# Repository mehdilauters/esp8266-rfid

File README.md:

# ID-12LA to tcp bridge
http://cdn.sparkfun.com/datasheets/Sensors/ID/ID-2LA,%20ID-12LA,%20ID-20LA2013-4-10.pdf

Configure your parameters in user/user_config.h

run on your server 

````
python /tmp/server.py 5555
starting up on 0.0.0.0 port 5555
waiting for a connection
client connected:waiting for a connection
 ('54.145.90.17', 44844)
tag 7800F011A6 received
tag 7800F8CC97 received
````

To enable the webui, please run ````bower install first````

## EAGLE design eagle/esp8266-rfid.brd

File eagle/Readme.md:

https://www.sparkfun.com/tutorials/119

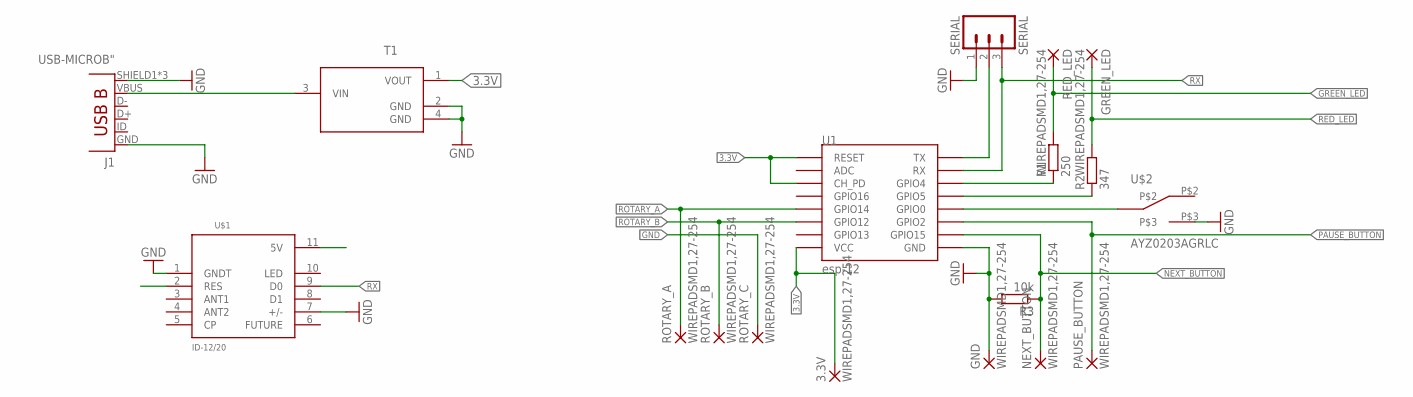
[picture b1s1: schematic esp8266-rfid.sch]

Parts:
3.3V: WIREPADSMD1,27-254; SMD1,27-2,54
GND: WIREPADSMD1,27-254; SMD1,27-2,54
GREEN_LED: WIREPADSMD1,27-254; SMD1,27-2,54
J1: USB-MICROB"; USB-B-MICRO-SMD_V03
NEXT_BUTTON: WIREPADSMD1,27-254; SMD1,27-2,54
PAUSE_BUTTON: WIREPADSMD1,27-254; SMD1,27-2,54
R1: 250; R0603
R2: 347; R0603
R3: 10k; R0603
RED_LED: WIREPADSMD1,27-254; SMD1,27-2,54
ROTARY_A: WIREPADSMD1,27-254; SMD1,27-2,54
ROTARY_B: WIREPADSMD1,27-254; SMD1,27-2,54
ROTARY_C: WIREPADSMD1,27-254; SMD1,27-2,54
SERIAL: SERIAL; 1X03
T1: L78L33ACUTR; SOT150P400X160-4N
U1: esp-12; ESP12-SMD
U$1: ID-12/20; ID-12
U$2: AYZ0203AGRLC

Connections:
3.3V: 3.3V.1, T1.1 (VOUT), U1.CH_PD, U1.RESET, U1.VCC
GND: GND.1, J1.GND, J1.SHIELD1 (SHIELD), J1.SHIELD2 (SHIELD), J1.SHIELD3 (SHIELD), R3.2, ROTARY_C.1, SERIAL.1, T1.2 (GND), T1.4 (GND), U1.GND, U$1.1 (GNDT), U$1.7 (+/-), U$2.P$3
GREEN_LED: R1.2, RED_LED.1
unnamed: U1.GPIO0, U$2.P$1 (COM)
unnamed: R1.1, U1.GPIO4
NEXT_BUTTON: NEXT_BUTTON.1, R3.1, U1.GPIO15
PAUSE_BUTTON: PAUSE_BUTTON.1, U1.GPIO2
RED_LED: GREEN_LED.1, R2.2
RESET: R2.1, U1.GPIO5
ROTARY_A: ROTARY_A.1, U1.GPIO14
ROTARY_B: ROTARY_B.1, U1.GPIO12
RX: SERIAL.3, U1.RXD0 (RX), U$1.9 (D0)
TX: SERIAL.2, U1.TXD0 (TX)
VBUS: J1.VBUS, T1.3 (VIN), U$1.2 (RES), U$1.11 (5V)

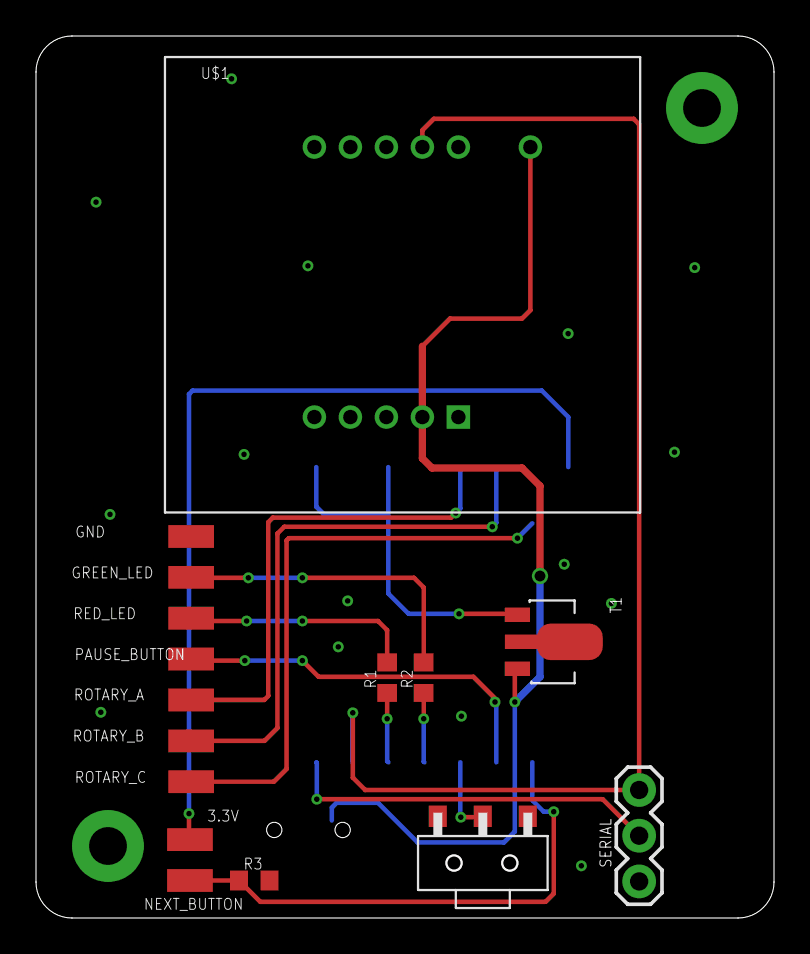
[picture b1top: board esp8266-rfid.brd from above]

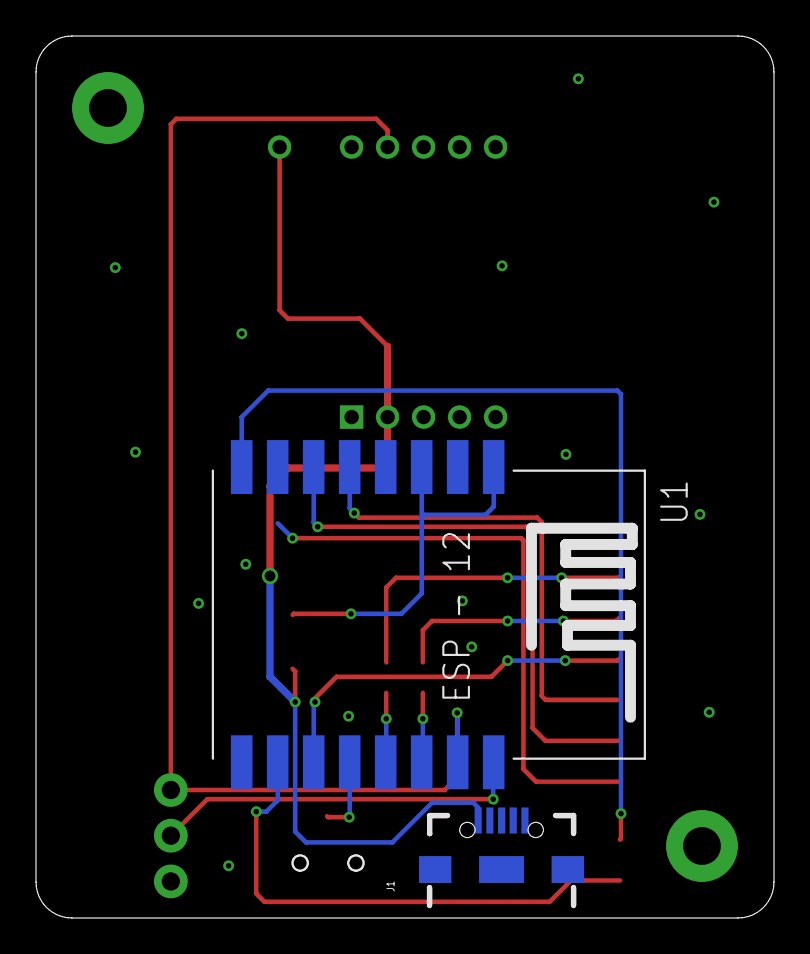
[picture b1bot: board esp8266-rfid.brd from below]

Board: 2 copper layers, 40.9 x 48.9 mm, 18 parts (2 on the bottom side), 14 nets.

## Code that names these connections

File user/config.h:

#ifndef CONFIG_HPP
#define CONFIG_HPP

#define DEFAULT_SSID "esp-rfid"

// should be firmwar_1.bin on the server
#define TFTP_IMAGE_FILENAME "esp-rfid.bin"

#define MAX_AP_DURATION 60

#define ALTERNATE_PUSH_PIN 0
#define PLAYPAUSE_PUSH_PIN 2
#define GREEN_LED_PIN 4
#define RED_LED_PIN 5

#define ROTARY_B 12
#define ROTARY_C 13
#define ROTARY_A 14

#define NEXT_PUSH_PIN 15



#define BUTTON_PRESSED_DELAY 100

#define UP_TAG "AF00AF00AC"
#define DOWN_TAG "AF00AF00AD"
#define NEXT_TAG "AF00AF00AE"
#define PAUSE_TAG "AF00AF00AF"

#define ALTERNATE_TAG "AF00AF00BA"
#define UP_ALTERNATE_TAG "AF00AF00BB"
#define DOWN_ALTERNATE_TAG "AF00AF00BC"
#define NEXT_ALTERNATE_TAG "AF00AF00BD"
#define PAUSE_ALTERNATE_TAG "AF00AF00BD"

#define RAW_TCP
#endif

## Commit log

2016-10-08 Serveur update
2016-10-08 RFIDServer
2016-10-08 New TCP connexion for each tag + virtal tag for button
2016-10-08 README
2016-10-08 missing file fix
2016-10-08 Default config file
2016-11-06 Adding EAGLE schematic
2016-11-11 EAGLE moved to new folder
2016-11-21 CONFIG: apmode if no config
2016-11-22 WEBUI: wifi settings begins to work
2016-11-23 WEBUI: parsing essid done
2016-11-23 WEBUI: working essid and passwprd setup
2016-11-24 WEBUI: saving server to flash
2016-11-25 WEBUI: security check + CONFIG: read server from flash
2016-11-28 WEBUI: adding current config
2016-11-28 WEBUI: captive portal configuration
2016-11-29 OTA: init
2016-12-01 SDK switch to rtos
2016-12-01 SDK switch WEBSERVER init
2016-12-05 WEBUI: parsing post request
2016-12-06 SDK: porting rfid.c
2016-12-07 ESP-12: update flash layout
2016-12-08 RFID: fix wifi hangs #1
2016-12-08 SDK: uart working
2016-12-15 OTA: first working solution
2016-12-19 APP: wifi task
2016-12-20 OTA: upgrade from client ip
2016-12-20 TEST prod
2016-12-21 TEST prod + upgrade check
2016-12-21 UPG from hmi: wip
2016-12-23 Serial number in HMI + baudrate
2016-12-23 OTA: upg fix
2016-12-27 EAGLE + http push
2016-12-27 EAGLE: rotary fix
2016-12-27 ROTARY init
2016-12-28 ROTARY_ENCODER + red led
2016-12-28 EAGLE: resistance value update
2016-12-29 LED: green led status
2016-12-29 TAG config + buttons
2016-12-30 KODI working
2016-12-31 BUTTONS + OTA green led
2016-12-31 BUILD: versionning
2017-04-20 DEEZER: get request fix
2017-04-28 MAIN: firmware name
2017-05-03 AP: switch off ap after MAX_DURATION
2017-07-30 BUTTONS: add alternate button
2017-07-30 warning fixes
2017-10-27 FreeRTOS update

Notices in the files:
parts and their libraries:
SparkFun-Connectors: Licensing: Creative Commons ShareAlike 4.0 International - https://creativecommons.org/licenses/by-sa/4.0
